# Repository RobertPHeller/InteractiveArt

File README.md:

# Interactive Art 

These are micro-processor based art projects where the viewer can interact in 
some way with the art.  These art items use Arduino and Arduino-like 
micro-processors to provide the "smarts" for the interactivity.

The projects include:

1. [Hello World](HelloWorld)
2. [Welcome To Gothem City](WelcomeToGothemCity)
3. [Paging Dr. Howard, Dr Fine, Dr. Howard](PagingDrHowardEtAl)
4. [Why Did The Chicken Cross The Street](WhyDidTheChicken)
5. [The Android's Dream](AndroidsDream)
6. [Only Her Hairdresser Knows For Sure](OnlyHerHairdresser)
7. [Sprocket Factory](SprocketFactory)
8. [Steel Wheels](SteelWheels)
9. [Stray Cats](StrayCats)

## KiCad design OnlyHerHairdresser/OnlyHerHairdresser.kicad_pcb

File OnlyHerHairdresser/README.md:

# Only Her Hairdresser Knows For Sure

This piece features a young lady who needs a little help deciding on a hair 
color.  The observer has a selection of hair colors to choose from.  By 
placing a selected "hair color box" (a painted wooden block) in the young 
lady's hand that color is applied to the fiber optic hair via RGB LEDs. The 
observer might want to try several selections.

## Processing Element

This piece uses an Adafruit Feather M0 Express.

## Components of Note

* Adafruit TCS34725  Breakout (Color Sensor).
* A MPQ3904 quad NPN driver transistor.
* Four 10mm RGB LEDs.
* Side glow fiber optics (used for the ``hair'').

## Additional Reading

* [_Fiber Optic Pixie Skirt_](https://learn.adafruit.com/fiber-optic-pixie-princess-skirt)
* [_Adafruit Color Sensors_](https://learn.adafruit.com/adafruit-color-sensors)

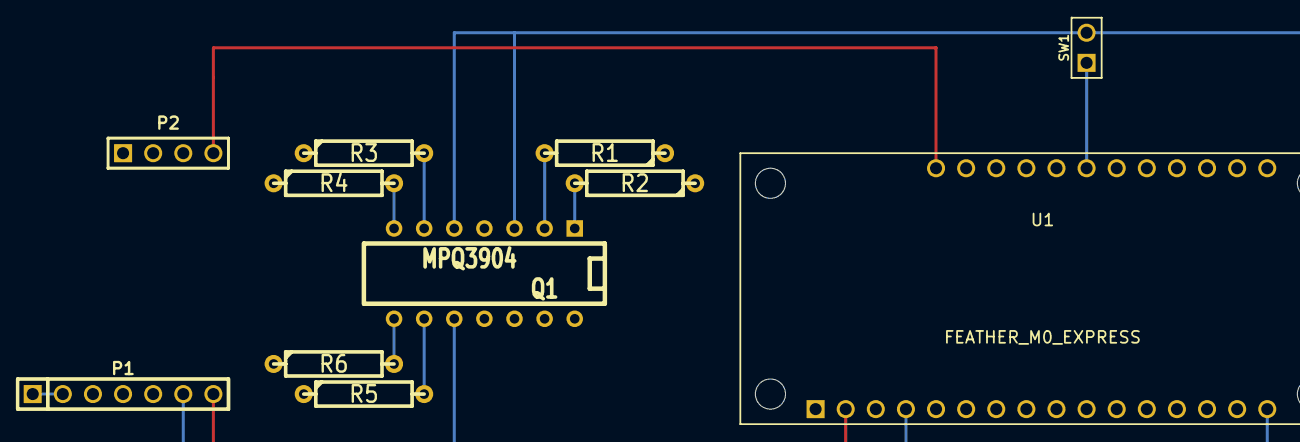
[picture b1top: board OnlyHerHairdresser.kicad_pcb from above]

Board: 6 copper layers, 11 parts (0 on the bottom side), 19 nets.

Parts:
P1: TCS34725 Breakout; PIN_ARRAY-7X1
P2: RGB LEDS; PIN_ARRAY_4x1
Q1: MPQ3904; DIP-14__300
R1, R3, R5: 1K Ohms; R4
R2, R4, R6: 45 Ohms; R4
SW1: SW_PUSH; PIN_ARRAY_2X1
U1: FEATHER_M0_EXPRESS; AdafruitFeather

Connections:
/B: P2.3, R6.1
/Comm: P2.4, U1.28
/G: P2.2, R4.1
/GND: P1.6, Q1.3, Q1.5, Q1.10, SW1.2, U1.4, U1.16
/INT: P1.1, P1.2
/R: P2.1, R2.1
/SCL: P1.4, U1.18
/SDA: P1.3, U1.17
/VIN: P1.7, U1.2
unnamed: Q1.1, R2.2
unnamed: Q1.7, R4.2
unnamed: Q1.8, R6.2
unnamed: SW1.1, U1.23
unnamed: Q1.2, R1.2
unnamed: Q1.9, R5.2
unnamed: R5.1, U1.19
unnamed: Q1.6, R3.2
unnamed: R3.1, U1.20
unnamed: R1.1, U1.22

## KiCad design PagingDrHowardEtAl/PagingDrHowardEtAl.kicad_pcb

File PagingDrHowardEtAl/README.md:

# Paging Dr. Howard, Dr. Fine, Dr. Howard

Oh dear, you are hospitalized with a bad case of humorititous. Fortunately,
the three top specialists of this condition are in residence and have agreed
to provide you with their world famous treatment. Dr. Moe Howard, Dr. Larry
Fine, and Dr. Curly Howard first need to check to see if you have a pulse
before you are wheeled into the operating theater, where they will operate on
your funny bone. Place your finger in the sensor hole and press down to check
your pulse.

## Processing Element

This piece uses a Arduino Uno processor.

## Components of Note

* World Famous Electronics Pulse Sensor
* Adafruit Bargraph Backpack
* Adafruit 7 segment backpack

## Additional Reading

* [_Super Awesome Sylvia Builds a Pulse Sensor Pendant_](https://makezine.com/2013/05/28/super-awesome-sylvia-builds-a-pulse-sensor-pendant/)
* [_Adafruit LED Backpacks_](https://learn.adafruit.com/adafruit-led-backpack/)

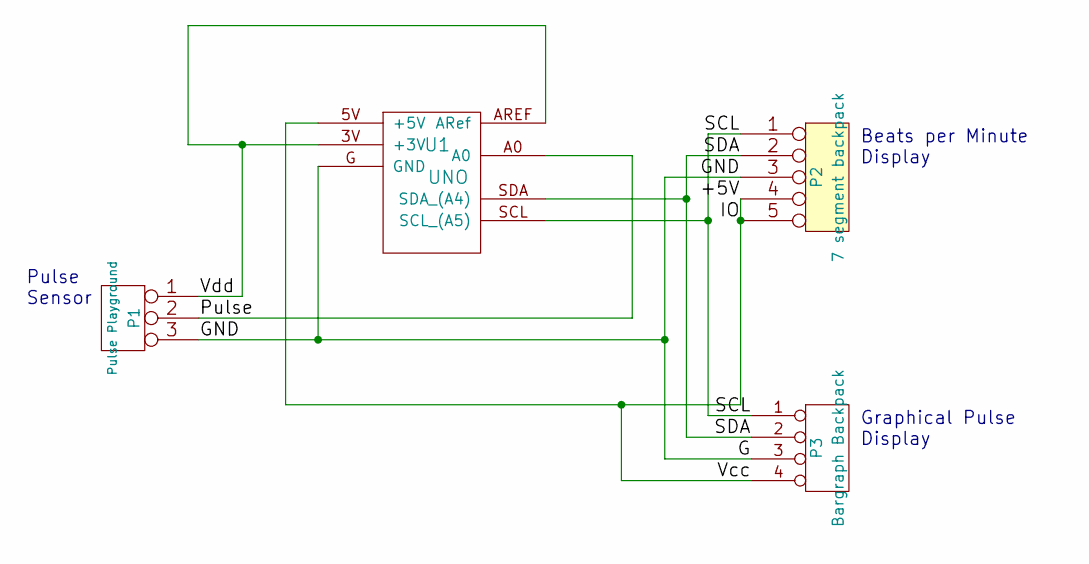
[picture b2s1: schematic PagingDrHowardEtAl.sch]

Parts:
P1: Pulse Playground
P2: 7 segment backpack
P3: Bargraph Backpack
U1: UNO

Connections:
/+5V: P2.4, P2.5, P3.4, U1.5V (+5V)
/G: P1.3, P2.3, P3.3, U1.G (GND)
/Pulse: P1.2 (PM), U1.A0
/SCL: P2.1, P3.1, U1.SCL (SCL_(A5))
/SDA: P2.2, P3.2, U1.SDA (SDA_(A4))
/Vdd: P1.1, U1.3V (+3V), U1.AREF (ARef)

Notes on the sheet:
Pulse Sensor
Beats per Minute Display
Graphical Pulse Display

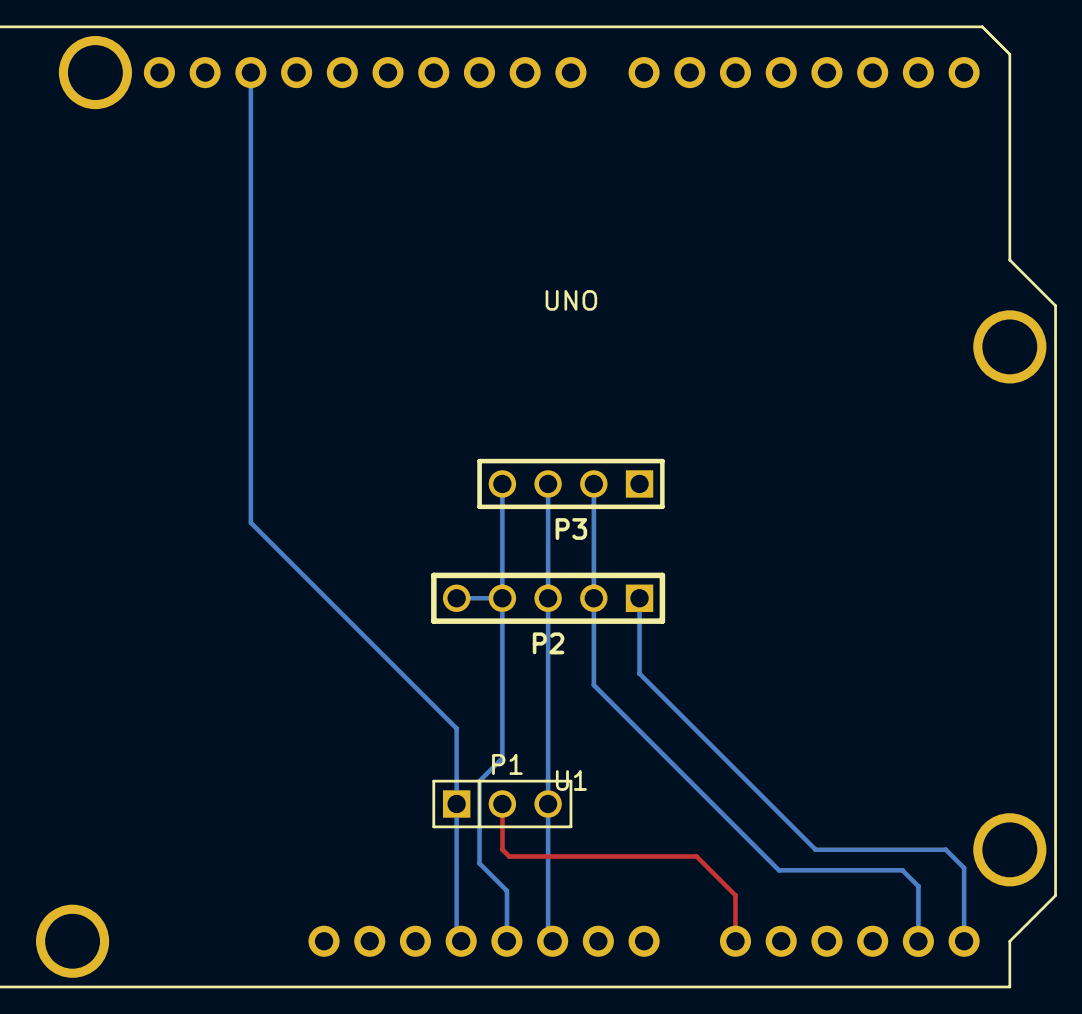
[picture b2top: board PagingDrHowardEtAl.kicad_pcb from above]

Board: 8 copper layers, 4 parts (0 on the bottom side), 6 nets.

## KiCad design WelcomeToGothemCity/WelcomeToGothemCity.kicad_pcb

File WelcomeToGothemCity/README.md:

# Welcome To Gothem City

Welcome to Gothem City, home of Batman and Robin. Oh no, the Bat Signal has
lit up the night as we get closer to the city. Does that mean there is a super
villain in town? See if you can find Batman and Robin or the super villain
(there may even be several). 

## Processing Element

This piece uses an Adafruit Metro Mini.

## Components of Note

* Adafruit Powerboost 1000c to provide extra power and to charge the battery.
* An SR04 ultrasonic range finder sensor.
* A TIP120 power transistor.
* A large number of yellow SMD LEDs to light up the Bat Signal.

## Additional Reading

* [_Distance Measurement with Ultrasound_](https://learn.adafruit.com/distance-measurement-ultrasound-hcsr04)

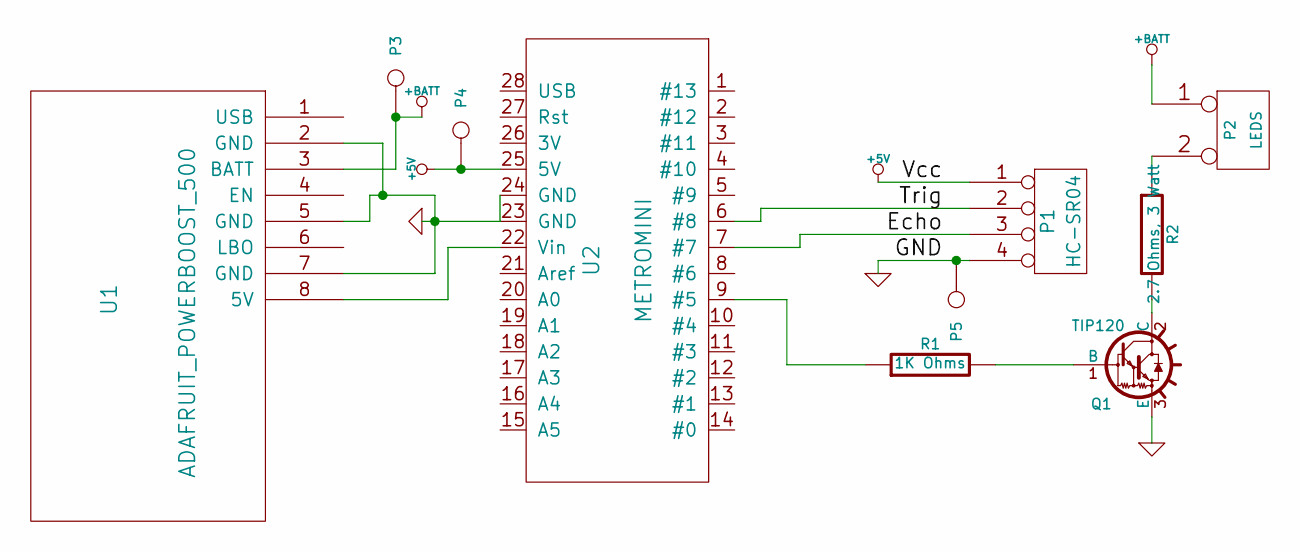
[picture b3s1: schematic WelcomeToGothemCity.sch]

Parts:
P1: HC-SR04
P2: LEDS
P3, P4, P5: CONN_1
Q1: TIP120; TO220
R1: 1K Ohms
R2: 2.7 Ohms, 3 Watt; Mouser Part Number 594-5093NW2R700J
U1: ADAFRUIT_POWERBOOST_500
U2: METROMINI

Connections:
+5V: P1.1, P4.1, U2.25 (5V)
+BATT: P2.1, P3.1, U1.3 (BATT)
/Echo: P1.3, U2.7 (#7)
/Trig: P1.2, U2.6 (#8)
GND: P1.4, P5.1, Q1.3 (E), U1.2 (GND), U1.5 (GND), U1.7 (GND), U2.23 (GND), U2.24 (GND)
unnamed: U1.8 (5V), U2.22 (Vin)
unnamed: P2.2 (PM), R2.1
unnamed: Q1.2 (C), R2.2
unnamed: Q1.1 (B), R1.2
unnamed: R1.1, U2.9 (#5)

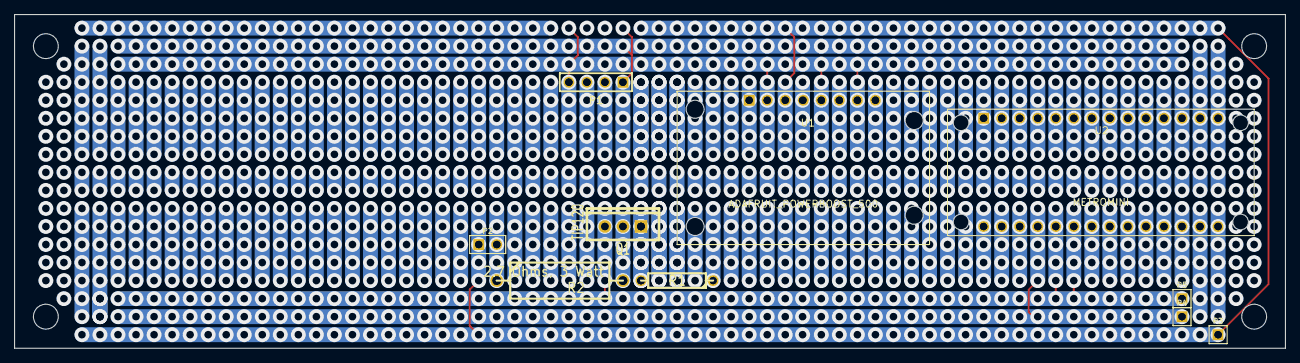
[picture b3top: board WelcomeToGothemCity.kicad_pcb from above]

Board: 8 copper layers, 179.0 x 47.0 mm, 10 parts (0 on the bottom side), 10 nets.

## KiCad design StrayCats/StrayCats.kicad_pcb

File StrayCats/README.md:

# Stray Cats

    Black and orange stray cat sittin' on a fence
    Ain't got enough dough to pay the rent
    I'm flat broke, but I don't care
    I strut right by with my tail in the air
    -- Brian Setzer

This piece features a small TV set that only gets channels featuring cats. Go 
ahead, use the remote to select a different channel.  Sorry, every channel 
features cats.

## Processing Element

This piece uses an Adafruit Feather M0 Express.

## Components of Note

* An Adafruit 1.8" TFT Display Breakout, that features a microSD card 
slot.
* An IR Detector and a mini remote control.

## Additional Reading

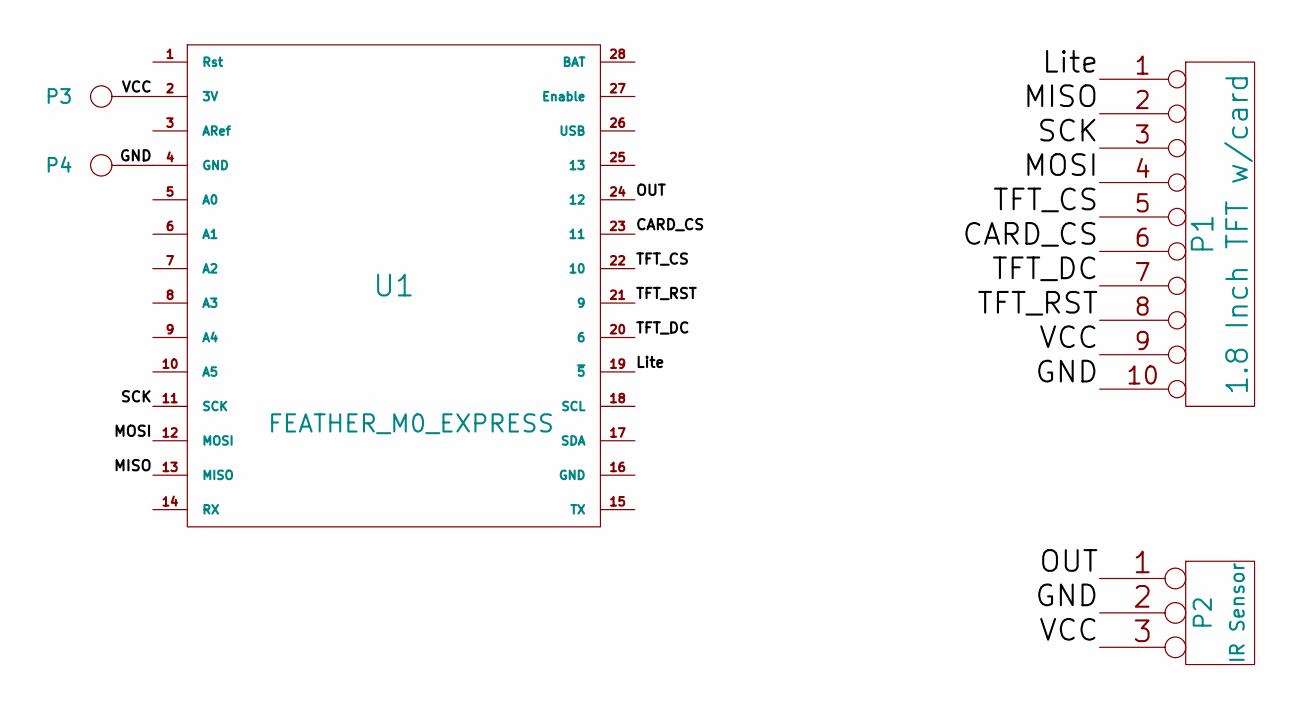
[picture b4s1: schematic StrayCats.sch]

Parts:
P1: 1.8 Inch TFT w/card
P2: IR Sensor
P3, P4: CONN_1
U1: FEATHER_M0_EXPRESS

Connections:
/CARD_CS: P1.6, U1.23 (11~)
/GND: P1.10, P2.2 (PM), P4.1, U1.4 (GND)
/Lite: P1.1, U1.19 (~5)
/MISO: P1.2, U1.13 (MISO)
/MOSI: P1.4, U1.12 (MOSI)
/OUT: P2.1, U1.24 (12)
/SCK: P1.3, U1.11 (SCK)
/TFT_CS: P1.5, U1.22 (10~)
/TFT_DC: P1.7, U1.20 (6)
/TFT_RST: P1.8, U1.21 (9~)
/VCC: P1.9, P2.3, P3.1, U1.2 (3V)

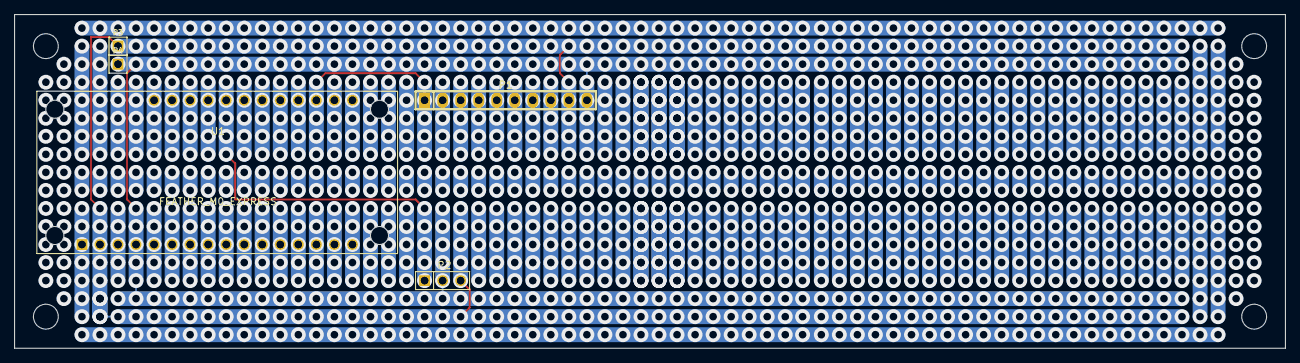
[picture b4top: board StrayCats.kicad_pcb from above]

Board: 8 copper layers, 179.0 x 47.0 mm, 5 parts (0 on the bottom side), 11 nets.

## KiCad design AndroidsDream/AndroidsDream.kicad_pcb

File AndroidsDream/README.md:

# The Androids Dream

This piece was inspired by the question posed in the title of a Philip K. Dick
novel, _Do Androids Dream Of Electric Sheep?_. This piece features an
electric sheep, so it is possibly what every android is dreaming of. This not
merely a stuffed sheep toy, it actually moves like a real sheep, but is
powered by electricity and not by grass (yes, the grass it is lying on is fake
too). Go ahead and pet it. It will raise its head and wag its tail. Don't you
wish you were an android so that this would be the answer to your dreams?

## Processing Element

This piece uses a 3V Adafruit Itsy Bitsy 32u4.

## Components of Note

* A pair of micro servos (to move the head and tail).
* Three Light Dependent Resistors (light sensors) to sense when it is dark
(sleep mode) or when being petted.
* Two micro servos to move the head and tail.

## Additional Reading

* [_Adafruit Trinket-Modded Stuffed Animal_](https://learn.adafruit.com/adafruit-trinket-modded-stuffed-animal)

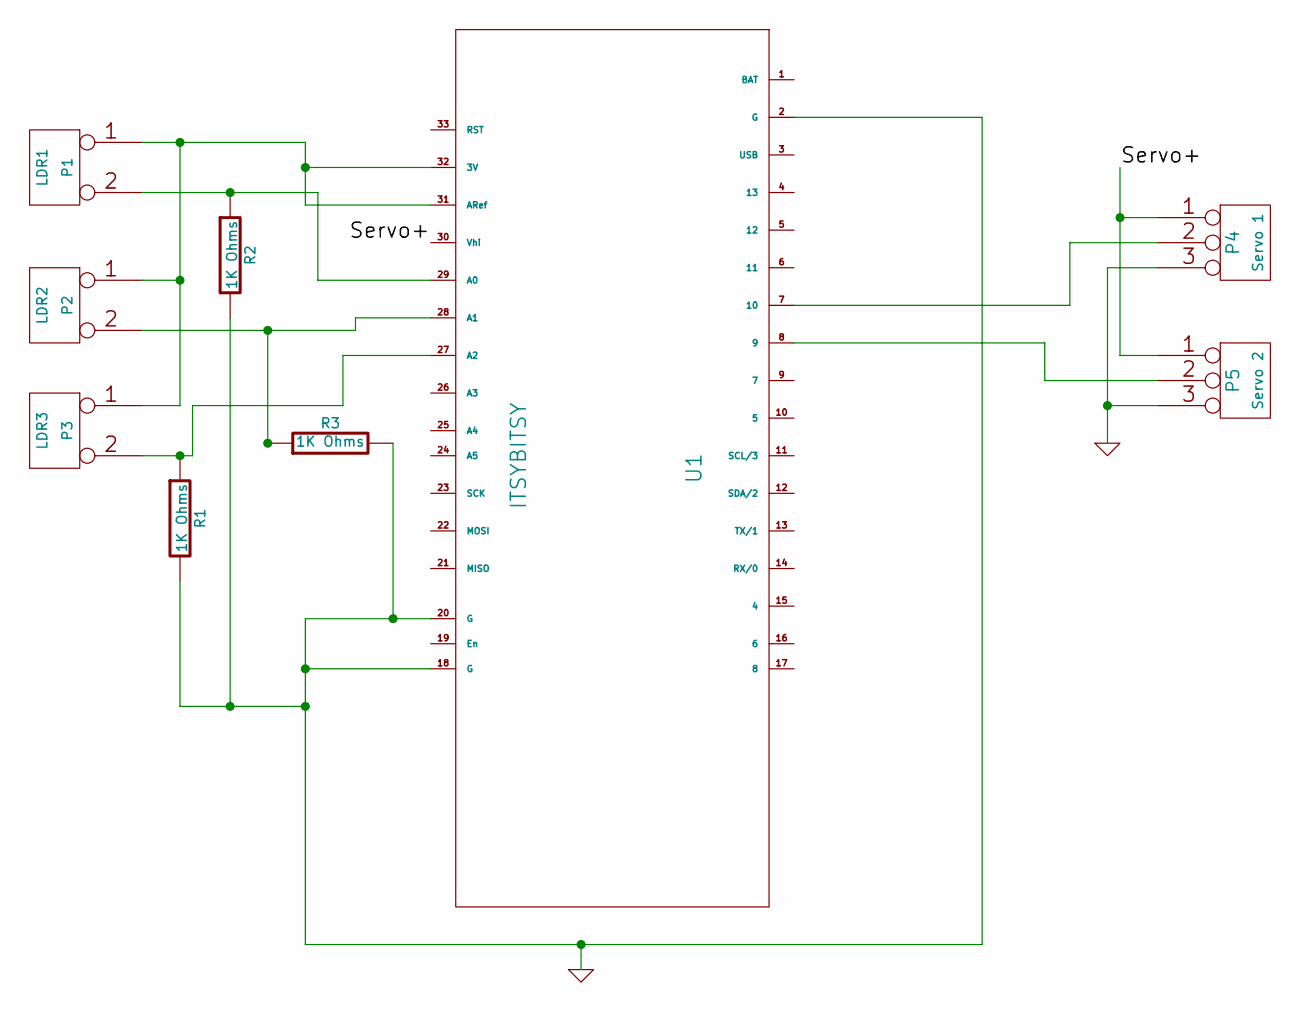
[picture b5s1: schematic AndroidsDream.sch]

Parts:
P1: LDR1
P2: LDR2
P3: LDR3
P4: Servo 1
P5: Servo 2
R1, R2, R3: 1K Ohms
U1: ITSYBITSY

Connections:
/Servo+: P4.1, P5.1, U1.30 (Vhi)
GND: P4.3, P5.3, R1.2, R2.2, R3.2, U1.2 (G), U1.18 (G), U1.20 (G)
unnamed: P4.2 (PM), U1.7 (10)
unnamed: P5.2 (PM), U1.8 (9)
unnamed: P1.1, P2.1, P3.1, U1.31 (ARef), U1.32 (3V)
unnamed: P2.2 (PM), R3.1, U1.28 (A1)
unnamed: P1.2 (PM), R2.1, U1.29 (A0)
unnamed: P3.2 (PM), R1.1, U1.27 (A2)

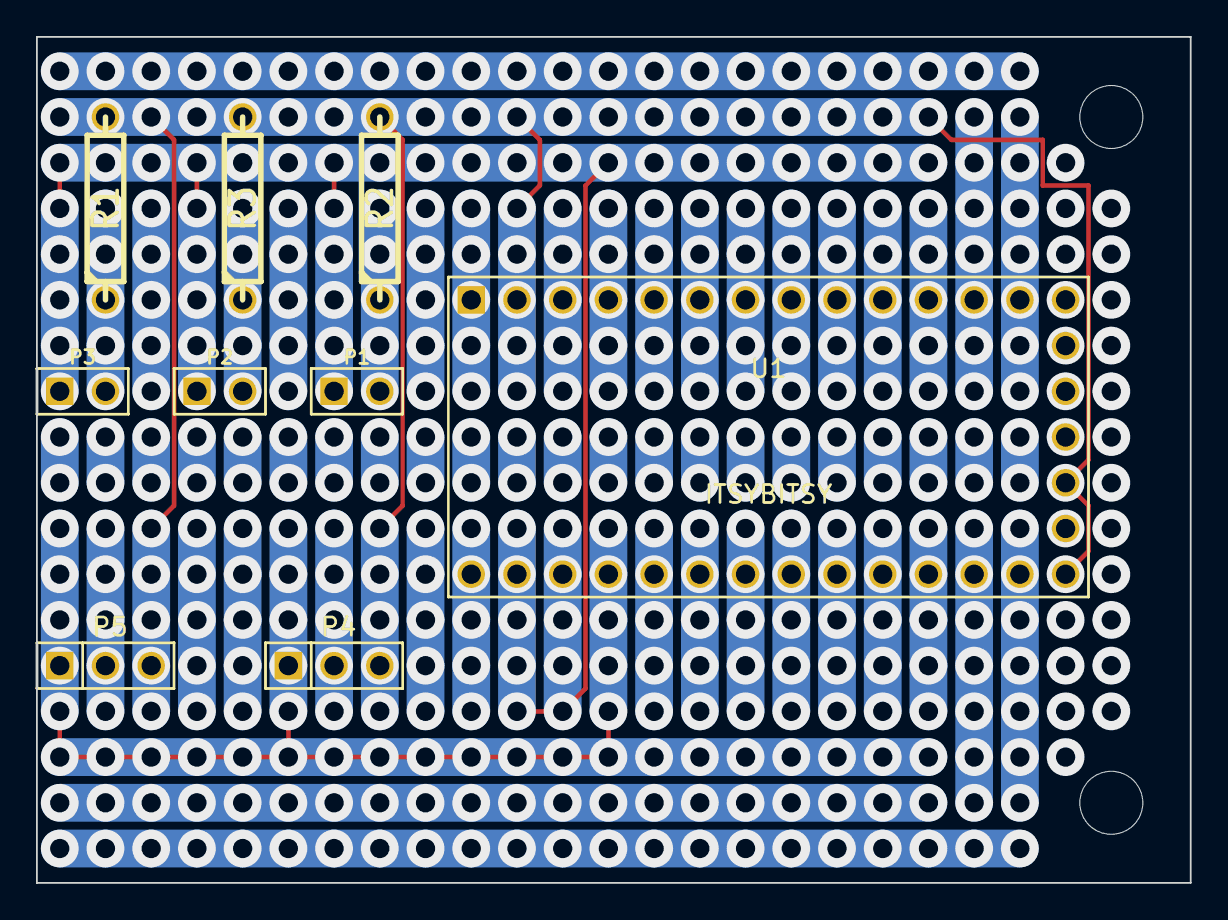
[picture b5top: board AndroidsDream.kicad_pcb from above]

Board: 8 copper layers, 64.1 x 47.0 mm, 9 parts (0 on the bottom side), 8 nets.

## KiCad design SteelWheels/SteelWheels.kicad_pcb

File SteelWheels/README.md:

# Steel Wheels

Great news, you have been hired to be the engineer of a steam locomotive. 
You get to use the throttle to make it go fast or slow.  Go ahead crank the 
throttle to its maximum.  Full stream ahead!

## Processing Element

This piece uses an Adafruit Metro Mini.

## Components of Note

* Two small twelve pixel Neopixel rings.
* Two large twenty four pixel Neopixel rings.
* One quarter segment giant Neopixel ring.

## Additional Reading}

* [_The Magic of NeoPixels_](https://learn.adafruit.com/adafruit-neopixel-uberguide)

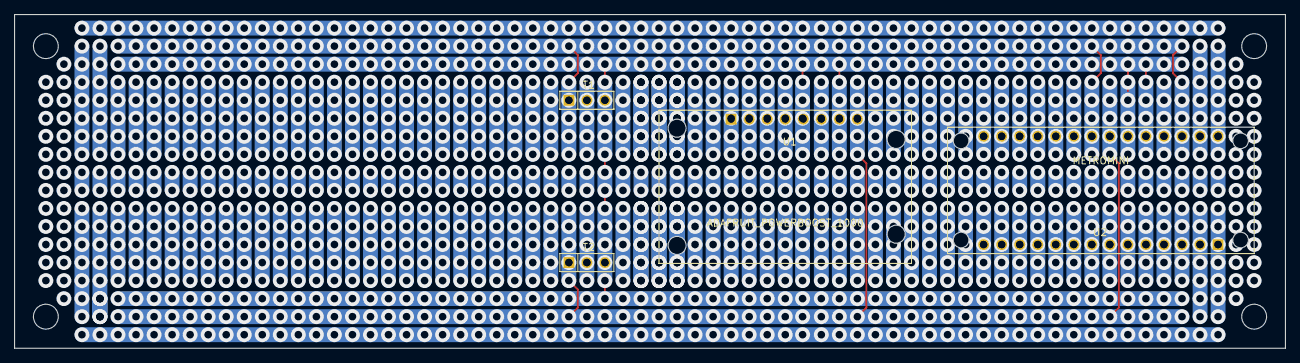
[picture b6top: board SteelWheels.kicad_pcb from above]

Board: 8 copper layers, 179.0 x 47.0 mm, 4 parts (0 on the bottom side), 5 nets.

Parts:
T1: Throttle; PIN_ARRAY_3X1
T2: Neopixels; PIN_ARRAY_3X1
U1: ADAFRUIT_POWERBOOST_1000; PBost500Breakout
U2: METROMINI; MetroMini

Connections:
+3.3V: T1.1, U2.21, U2.26
+5V: T2.1, U1.8, U2.22
/ThrottleIn: T1.2, U2.20
GND: T1.3, T2.3, U1.5, U1.7, U2.23, U2.24
unnamed: T2.2, U2.8

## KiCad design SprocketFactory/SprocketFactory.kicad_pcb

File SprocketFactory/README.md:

# Sprocket Factory

Congratulations, you have been promoted to VP of Production at the sprocket
factory. You job consists of pressing the Start button promptly at 9:00am each
morning and then pressing the Stop button promptly at 5:00pm each evening. Go
ahead press the start button now to get the fully automated factory going.
Don't forget to press the Stop button before you leave for the day.

## Processing Element

This piece uses an Adafruit Feather M0 Express.

## Components of Note

* Adafruit 8 channel PWM or Servo Feather Wing.
* Adafruit Powerboost 1000c.
* 8 Micro Servos

## Additional Reading

* [_Adafruit 8-Channel PWM or Servo FeatherWing_](https://learn.adafruit.com/adafruit-8-channel-pwm-or-servo-featherwing)

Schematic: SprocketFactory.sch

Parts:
SW1: Start
SW2: Stop
U1: FEATHER_M0_EXPRESS
U2: 8-CHANNELSERVO​FEATHERWING
U3: ADAFRUIT_POWERBOOST_500

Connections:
/3V: U1.2 (3V), U2.2
/5: SW2.1, U1.19 (~5), U2.19
/6: SW1.1, U1.20 (6), U2.20
/9: U1.21 (9~), U2.21
/10: U1.22 (10~), U2.22
/11: U1.23 (11~), U2.23
/12: U1.24 (12), U2.24
/13: U1.25 (13), U2.25
/A0: U1.5 (A0), U2.5
/A1: U1.6 (A1), U2.6
/A2: U1.7 (A2), U2.7
/A3: U1.8 (A3), U2.8
/A4: U1.9 (A4), U2.9
/A5: U1.10 (A5), U2.10
/ARef: U1.3 (ARef), U2.3
/BAT: U1.28 (BAT), U2.28, U3.3 (BATT)
/Enable: U1.27 (Enable), U2.27
/GND: SW1.2, SW2.2, U1.4 (GND), U1.16 (GND), U2.4, U2.16, U2.SP-, U3.2 (GND), U3.5 (GND), U3.7 (GND)
/MISO: U1.13 (MISO), U2.13
/MOSI: U1.12 (MOSI), U2.12
/RX: U1.14 (RX), U2.14
/Rst: U1.1 (Rst), U2.1
/SCK: U1.11 (SCK), U2.11
/SCL: U1.18 (SCL), U2.18
/SDA: U1.17 (SDA), U2.17
/TX: U1.15 (TX), U2.15
/USB: U1.26 (USB), U2.26
unnamed: U2.SP+, U3.8 (5V)

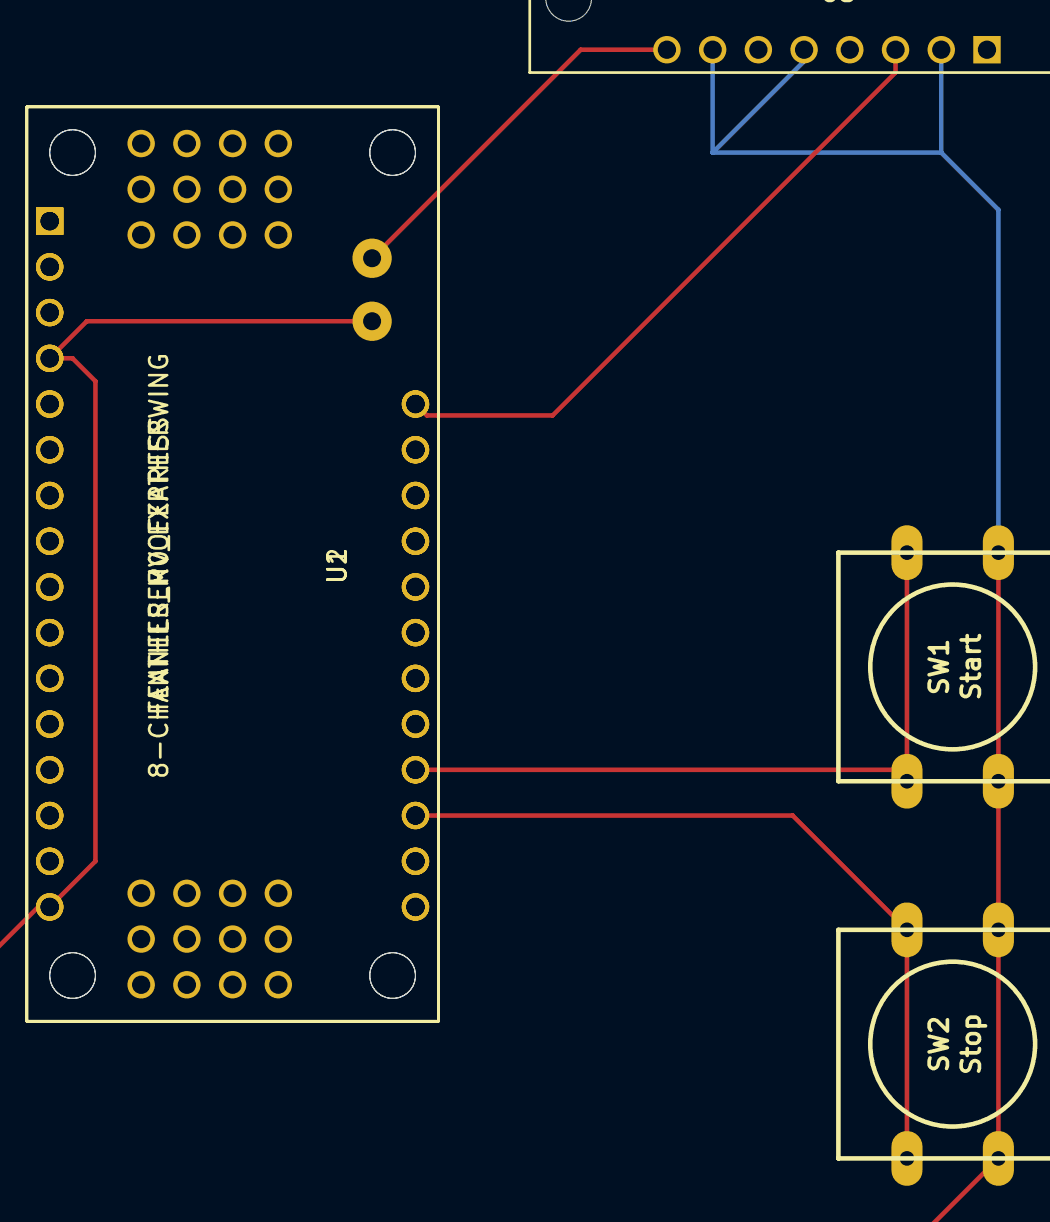
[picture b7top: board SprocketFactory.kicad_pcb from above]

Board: 2 copper layers, 5 parts (0 on the bottom side), 28 nets.

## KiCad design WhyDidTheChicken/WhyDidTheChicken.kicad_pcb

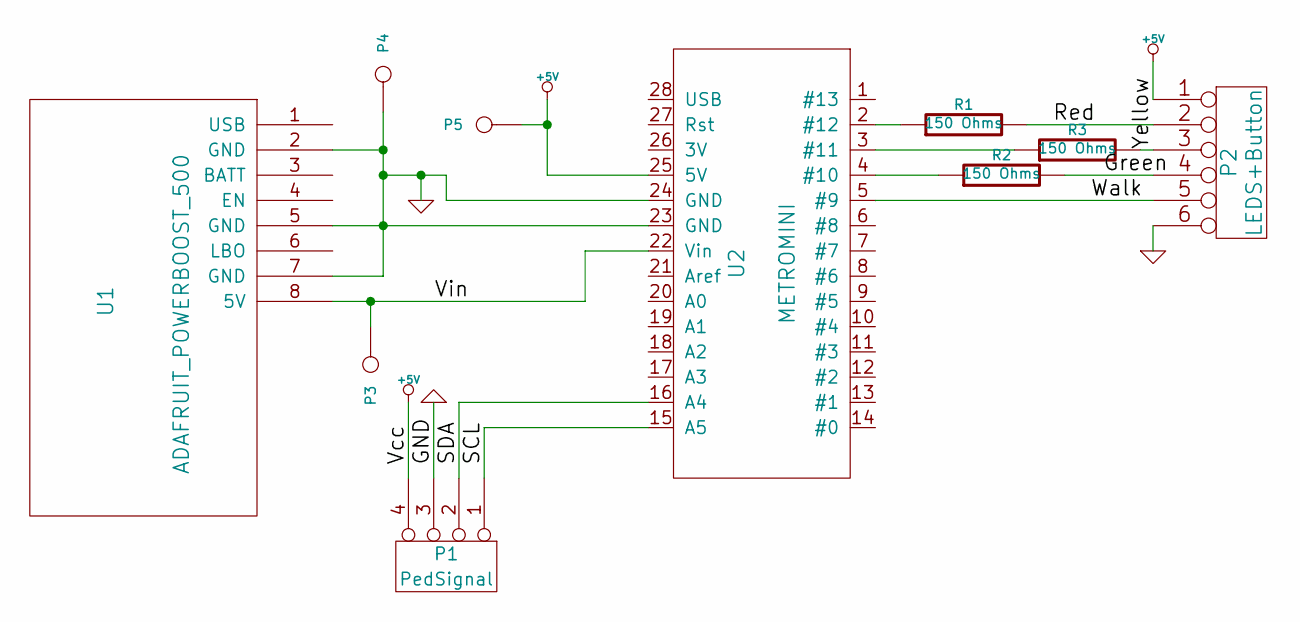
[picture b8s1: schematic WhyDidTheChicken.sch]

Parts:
P1: PedSignal
P2: LEDS+Button
P3, P4, P5: CONN_1
R1, R2, R3: 150 Ohms
U1: ADAFRUIT_POWERBOOST_500
U2: METROMINI

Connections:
+5V: P1.4, P2.1, P5.1, U2.25 (5V)
/Green: P2.4, R2.2
/Red: P2.2, R1.2
/SCL: P1.1, U2.15 (A5)
/SDA: P1.2, U2.16 (A4)
/Vin: P3.1, U1.8 (5V), U2.22 (Vin)
/Walk: P2.5, U2.5 (#9)
/Yellow: P2.3, R3.2
GND: P1.3, P2.6, P4.1, U1.2 (GND), U1.5 (GND), U1.7 (GND), U2.23 (GND), U2.24 (GND)
unnamed: R2.1, U2.4 (#10)
unnamed: R3.1, U2.3 (#11)
unnamed: R1.1, U2.2 (#12)

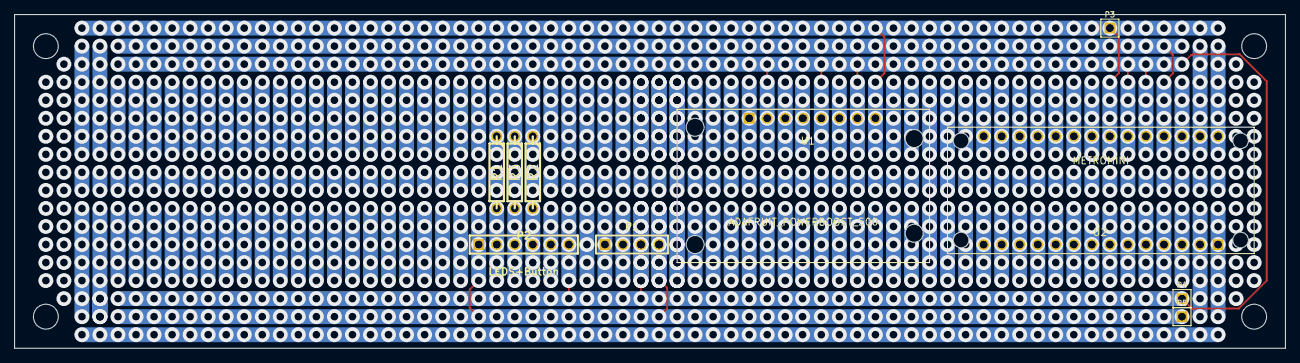
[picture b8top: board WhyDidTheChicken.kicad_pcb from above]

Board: 8 copper layers, 179.0 x 47.0 mm, 10 parts (0 on the bottom side), 12 nets.

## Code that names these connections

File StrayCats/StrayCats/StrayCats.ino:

// -!- C++ -!- //////////////////////////////////////////////////////////////
//
//  System        : 
//  Module        : 
//  Object Name   : $RCSfile$
//  Revision      : $Revision$
//  Date          : $Date$
//  Author        : $Author$
//  Created By    : $USER_NAME$
//  Created       : $ASCII_TIME$
//  Last Modified : <181229.1757>
//
//  Description	
//
//  Notes
//
//  History
//	
/////////////////////////////////////////////////////////////////////////////
//
//    Copyright (C) $YEAR$  Robert Heller D/B/A Deepwoods Software
//			51 Locke Hill Road
//			Wendell, MA 01379-9728
//
//    This program is free software; you can redistribute it and/or modify
//    it under the terms of the GNU General Public License as published by
//    the Free Software Foundation; either version 2 of the License, or
//    (at your option) any later version.
//
//    This program is distributed in the hope that it will be useful,
//    but WITHOUT ANY WARRANTY; without even the implied warranty of
//    MERCHANTABILITY or FITNESS FOR A PARTICULAR PURPOSE.  See the
//    GNU General Public License for more details.
//
//    You should have received a copy of the GNU General Public License
//    along with this program; if not, write to the Free Software
//    Foundation, Inc., 675 Mass Ave, Cambridge, MA 02139, USA.
//
// 
//
//////////////////////////////////////////////////////////////////////////////

static const char rcsid[] = "@(#) : $Id$";

#include <Adafruit_ST7735.h>
#include <Adafruit_GFX.h>
#include <SD.h>
#include "IRRemote.h"
#include <string.h>

#define CARD_CS 11
#define TFT_CS  10
#define TFT_RST  9
#define TFT_DC   6
#define Lite     5

Adafruit_ST7735 display = Adafruit_ST7735(TFT_CS,TFT_DC,TFT_RST);
RemoteControl remote = RemoteControl();

int brightness;

// This function opens a Windows Bitmap (BMP) file and
// displays it at the given coordinates.  It's sped up
// by reading many pixels worth of data at a time
// (rather than pixel by pixel).  Increasing the buffer
// size takes more of the Arduino's precious RAM but
// makes loading a little faster.  20 pixels seems a
// good balance.

#define BUFFPIXEL 20

void bmpDraw(char *filename, uint8_t x, uint8_t y) {

  File     bmpFile;
  int      bmpWidth, bmpHeight;   // W+H in pixels
  uint8_t  bmpDepth;              // Bit depth (currently must be 24)
  uint32_t bmpImageoffset;        // Start of image data in file
  uint32_t rowSize;               // Not always = bmpWidth; may have padding
  uint8_t  sdbuffer[3*BUFFPIXEL]; // pixel buffer (R+G+B per pixel)
  uint8_t  buffidx = sizeof(sdbuffer); // Current position in sdbuffer
  boolean  goodBmp = false;       // Set to true on valid header parse
  boolean  flip    = true;        // BMP is stored bottom-to-top
  int      w, h, row, col;
  uint8_t  r, g, b;
  uint32_t pos = 0, startTime = millis();

  if((x >= display.width()) || (y >= display.height())) return;

  Serial.println();
  Serial.print("Loading image '");
  Serial.print(filename);
  Serial.println('\'');

  // Open requested file on SD card
  if ((bmpFile = SD.open(filename)) == NULL) {
    Serial.print("File not found");
    return;
  }

  // Parse BMP header
  if(read16(bmpFile) == 0x4D42) { // BMP signature
    Serial.print("File size: "); Serial.println(read32(bmpFile));
    (void)read32(bmpFile); // Read & ignore creator bytes
    bmpImageoffset = read32(bmpFile); // Start of image data
    Serial.print("Image Offset: "); Serial.println(bmpImageoffset, DEC);
    // Read DIB header
    Serial.print("Header size: "); Serial.println(read32(bmpFile));
    bmpWidth  = read32(bmpFile);
    bmpHeight = read32(bmpFile);
    if(read16(bmpFile) == 1) { // # planes -- must be '1'
      bmpDepth = read16(bmpFile); // bits per pixel
      Serial.print("Bit Depth: "); Serial.println(bmpDepth);
      if((bmpDepth == 24) && (read32(bmpFile) == 0)) { // 0 = uncompressed

        goodBmp = true; // Supported BMP format -- proceed!
        Serial.print("Image size: ");
        Serial.print(bmpWidth);
        Serial.print('x');
        Serial.println(bmpHeight);

        // BMP rows are padded (if needed) to 4-byte boundary
        rowSize = (bmpWidth * 3 + 3) & ~3;

        // If bmpHeight is negative, image is in top-down order.
        // This is not canon but has been observed in the wild.
        if(bmpHeight < 0) {
          bmpHeight = -bmpHeight;
          flip      = false;
        }

        // Crop area to be loaded
        w = bmpWidth;
        h = bmpHeight;
        if((x+w-1) >= display.width())  w = display.width()  - x;
        if((y+h-1) >= display.height()) h = display.height() - y;

        // Set TFT address window to clipped image bounds
        display.setAddrWindow(x, y, x+w-1, y+h-1);

        for (row=0; row<h; row++) { // For each scanline...

          // Seek to start of scan line.  It might seem labor-
          // intensive to be doing this on every line, but this
          // method covers a lot of gritty details like cropping
          // and scanline padding.  Also, the seek only takes
          // place if the file position actually needs to change
          // (avoids a lot of cluster math in SD library).
          if(flip) // Bitmap is stored bottom-to-top order (normal BMP)
            pos = bmpImageoffset + (bmpHeight - 1 - row) * rowSize;
          else     // Bitmap is stored top-to-bottom
            pos = bmpImageoffset + row * rowSize;
          if(bmpFile.position() != pos) { // Need seek?
            bmpFile.seek(pos);
            buffidx = sizeof(sdbuffer); // Force buffer reload
          }

          for (col=0; col<w; col++) { // For each pixel...
            // Time to read more pixel data?
            if (buffidx >= sizeof(sdbuffer)) { // Indeed
              bmpFile.read(sdbuffer, sizeof(sdbuffer));
              buffidx = 0; // Set index to beginning
            }

            // Convert pixel from BMP to TFT format, push to display
            b = sdbuffer[buffidx++];
            g = sdbuffer[buffidx++];
            r = sdbuffer[buffidx++];
            display.pushColor(display.Color565(r,g,b));
          } // end pixel
        } // end scanline
        Serial.print("Loaded in ");
        Serial.print(millis() - startTime);
        Serial.println(" ms");
      } // end goodBmp
    }
  }

  bmpFile.close();
  if(!goodBmp) Serial.println("BMP format not recognized.");
}

// These read 16- and 32-bit types from the SD card file.
// BMP data is stored little-endian, Arduino is little-endian too.
// May need to reverse subscript order if porting elsewhere.

uint16_t read16(File f) {
  uint16_t result;
  ((uint8_t *)&result)[0] = f.read(); // LSB
  ((uint8_t *)&result)[1] = f.read(); // MSB
  return result;
}

uint32_t read32(File f) {
  uint32_t result;
  ((uint8_t *)&result)[0] = f.read(); // LSB
  ((uint8_t *)&result)[1] = f.read();
  ((uint8_t *)&result)[2] = f.read();
  ((uint8_t *)&result)[3] = f.read(); // MSB
  return result;
}

#define LEARN

void setup() {
    SD.begin(CARD_CS);
#ifdef LEARN
    Serial.begin(9600);
    while (!Serial) {
        ; // wait for serial port to connect. Needed for native USB port only
    }
    Serial.println("Learn Mode...");
    remote.storePulses("VolM",'v');
    remote.storePulses("PlayPause",'p');
    remote.storePulses("VolP",'V');
    remote.storePulses("Setup",'s');
    remote.storePulses("Prev",'<');
    remote.storePulses("Stop",'S');
    remote.storePulses("ChM",'c');
    remote.storePulses("Enter",'e');
    remote.storePulses("ChP",'C');
    remote.storePulses("Zero",'0');
    remote.storePulses("Next",'>');
    remote.storePulses("Back",'b');
    remote.storePulses("One",'1');
    remote.storePulses("Two",'2');
    remote.storePulses("Three",'3');
    remote.storePulses("Four",'4');
    remote.storePulses("Five",'5');
    remote.storePulses("Six",'6');
    remote.storePulses("Seven",'7');
    remote.storePulses("Eight",'8');
    remote.storePulses("Nine",'9');
    Serial.println("Done");
#else
    brightness = 0;
    pinMode(Lite,OUTPUT);
    // Use this initializer if you're using a 1.8" TFT
    display.initR(INITR_BLACKTAB);
    display.setRotation(1); // Check...
#endif
}

void loop() {
#ifdef LEARN
    delay(10000);
#else
    int key = remote.listen();
    if (key < 0) {
        if (brightness > 0) {
            brightness--;
            analogWrite(Lite,brightness);
        }
    } else {
        char imagefile[10];
        strcpy(imagefile,"image_");
        imagefile[6] = key;
        strcpy(&imagefile[7],".bmp");
        bmpDraw(imagefile,0,0);
        brightness = 255;
        analogWrite(Lite,brightness);
    }
    delay(500);
#endif
}

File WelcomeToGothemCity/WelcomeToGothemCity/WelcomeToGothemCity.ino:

// -!- C++ -!- //////////////////////////////////////////////////////////////
//
//  System        : 
//  Module        : 
//  Object Name   : $RCSfile$
//  Revision      : $Revision$
//  Date          : $Date$
//  Author        : $Author$
//  Created By    : $USER_NAME$
//  Created       : $ASCII_TIME$
//  Last Modified : <190729.0003>
//
//  Description	
//
//  Notes
//
//  History
//	
/////////////////////////////////////////////////////////////////////////////
//
//    Copyright (C) $YEAR$  Robert Heller D/B/A Deepwoods Software
//			51 Locke Hill Road
//			Wendell, MA 01379-9728
//
//    This program is free software; you can redistribute it and/or modify
//    it under the terms of the GNU General Public License as published by
//    the Free Software Foundation; either version 2 of the License, or
//    (at your option) any later version.
//
//    This program is distributed in the hope that it will be useful,
//    but WITHOUT ANY WARRANTY; without even the implied warranty of
//    MERCHANTABILITY or FITNESS FOR A PARTICULAR PURPOSE.  See the
//    GNU General Public License for more details.
//
//    You should have received a copy of the GNU General Public License
//    along with this program; if not, write to the Free Software
//    Foundation, Inc., 675 Mass Ave, Cambridge, MA 02139, USA.
//
// 
//
//////////////////////////////////////////////////////////////////////////////

static const char rcsid[] = "@(#) : $Id$";

// SR04 Data pins
const int TRIG_PIN = 8;
const int ECHO_PIN = 7;
// LEDs pin
const int LEDS     = 5;


// Anything over 400 cm (23200 us pulse) is "out of range"
const unsigned int MAX_DIST = 23200;

// Distance thresholds
const float CLOSE_INCHES = 2.5;
const float NEAR_INCHES  = 5.0;
const float FAR_INCHES   = 10.0;
const float VERY_FAR_INCHES = 15.0;
const float DISTANT_INCHES  = 30.0;


//**************************************************************
//* Setup: set pinmodes, turn off LEDs                         *
//**************************************************************
void setup() {
    Serial.begin(9600);
    // The Trigger pin will tell the sensor to range find
    pinMode(TRIG_PIN, OUTPUT);
    pinMode(ECHO_PIN, INPUT);
    digitalWrite(TRIG_PIN, LOW);
    
    pinMode(LEDS, OUTPUT);
    pinMode(LED_BUILTIN, OUTPUT);
    //digitalWrite(LEDS,0);
    analogWrite(LEDS,0);
}

//**************************************************************
//* Main Loop:  Trigger the sensor and retreive a result pulse *
//*             Compute the pulse width to measure the distance*
//*             Compare the measured distance to the thresholds*
//*             and light the LEDs to the selected brightness. *
//**************************************************************
void loop() {
    unsigned long t1;
    unsigned long t2;
    unsigned long pulse_width;
    float cm;
    float inches;
    
    // Hold the trigger pin high for at least 10 us
    digitalWrite(TRIG_PIN, HIGH);
    delayMicroseconds(10);
    digitalWrite(TRIG_PIN, LOW);
    
    // Wait for pulse on echo pin
    while ( digitalRead(ECHO_PIN) == 0 );
    
    // Measure how long the echo pin was held high (pulse width)
    // Note: the micros() counter will overflow after ~70 min
    t1 = micros();
    while ( digitalRead(ECHO_PIN) == 1);
    t2 = micros();
    pulse_width = t2 - t1;
    
    //Serial.print("*** pulse_width = ");Serial.println(pulse_width);
    // Calculate distance in centimeters and inches. The constants
    // are found in the datasheet, and calculated from the assumed speed 
    //of sound in air at sea level (~340 m/s).
    inches = pulse_width / 148.0;
    
    //Serial.print("*** inch = ");Serial.println(inches);
    // Measure thresholds and light the LEDs to the brightness called for.
    if (inches < CLOSE_INCHES) {
        //digitalWrite(LEDS,1);
        digitalWrite(LED_BUILTIN,1);
        Serial.println("CLOSE_INCHES");
        analogWrite(LEDS,255); // Very close, full brightness
    } else if (inches < NEAR_INCHES) {
        //digitalWrite(LEDS,1);
        digitalWrite(LED_BUILTIN,1);
        Serial.println("NEAR_INCHES");
        analogWrite(LEDS,192); // Pretty near, medium bright
    } else if (inches < FAR_INCHES) {
        Serial.println("FAR_INCHES");
        analogWrite(LEDS,128); // Fairly far, low brightness
    } else if (inches < VERY_FAR_INCHES) {
        Serial.println("VERY_FAR_INCHES");
        analogWrite(LEDS,64); // Very far, dim
    } else if (inches < DISTANT_INCHES) {
        Serial.println("DISTANT_INCHES");
        analogWrite(LEDS,32); // Very, very far very dim
    } else {
        Serial.println("Beyond DISTANT_INCHES");
        //digitalWrite(LEDS,0);
        digitalWrite(LED_BUILTIN,0);
        analogWrite(LEDS,0);  // Too far, totally dark
    }
    delay(100); // Check again in a 1/10 of a second.
}

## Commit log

2018-06-27 Initialize Repository
2018-06-27 Title list
2018-06-29 Create modules for Adafuit parts
2018-06-29 Create some of the piece projects
2018-10-22 (Re-)Initialize project
2018-10-24 Add Arduno project sketches.
2018-10-24 Complete infrastructure reorganization.
2018-10-25 HelloWorld Bitmap library.
2018-10-25 Final tweaks to the Hello World circuit.
2018-10-25 Hello World firmware completed.
2018-10-25 Add Comment headers to sketches.
2018-10-26 Complete Welcome To Gothem City
2018-10-26 Minor tweaks to WelcomeToGothemCity
2018-10-28 Complete two more: WelcomeToGothemCity and WhyDidTheChicken
2018-11-01 Completed SprocketFactory
2018-11-01 Update WelcomeToGothemCity: actual value for R2
2018-11-03 OnlyHerHairdresser: circuit designed and board laid out
2018-11-03 Completed code for OnlyHerHairdresser
2018-11-03 Minor tweaks to OnlyHerHairdresser
2018-11-03 Final debugging of Hello_World code.
2018-11-04 Completed SteelWheels
2018-11-05 Completed AndoidsDream.
2018-11-05 Complete PagingDrHowardEtAl
2018-11-06 Create cityscape generator
2018-11-06 Include variable initialization in setup()
2018-11-07 Additional tweaks to GenerateGothemCity.tcl
2018-11-07 Create program to blow up THE-THREE-STOOGES
2018-11-07 Generialize Enlarge.tcl
2018-11-08 Rename Hello_World to HelloWorld
2018-11-08 Start work on writeups
2018-11-08 Continue work on writeups
2018-11-09 Add QR Codes for all of the URLs
2018-11-10 Completed first draft of writups
2018-11-10 Include makefile for writups
2018-11-10 Continue writeups
2018-11-10 Rename misspelled directory and file names (AndoidsDream => AndroidsDream)
2018-11-10 Complete draft of writeup, with additional reading sections.
2018-11-11 Tweaks to the writups
2018-11-11 Add contact info to writeup
2018-11-11 Add PDFs of the Schematics
2018-11-11 Add detailed comments to both the code and the schematics
2018-11-11 Add 30ms debounce delay
2018-12-01 Add personal website to writeup, minor typos fixed in the writeup.
2018-12-04 Tweaks to writeup
2018-12-05 Minor fixes to WelcomeToGothemCity PCB
2018-12-29 Add the StrayCats piece.
2018-12-29 Minor update to StrayCats.ino
2019-01-13 Update WelcomeToGothemCity PCB (correct orientation of SR04 connector).
2019-01-17 Update TheGamesAFoot code.
2019-01-17 Fix transistor module (correct pin ordering).
2019-08-03 Add villian images, etc.
2019-08-04 Final debugging of WelcomeToGothemCity.
2019-08-27 Improved Hello World.
2019-08-27 Update PagingDrHowardEtAl.
2019-08-27 Revert "Improved Hello World."
    This reverts commit 9cfeab49f8a40077d410afd7f5da9c114483a884.
2019-08-27 Revert "Revert "Improved Hello World.""
    This reverts commit 68956442f3c98f9f4d55407133d2008b60599163.
2019-08-27 Revert "Update PagingDrHowardEtAl."
    This reverts commit db79b4fbad0fb7acf435444e0c859a0f028222a4.
2019-08-27 Corrected version of PagingDrHowardEtAl.
2019-08-27 Corrected version of PagingDrHowardEtA.
2019-08-28 PagingDrHowardEtAl, using an UNO R3
2019-08-29 Finalized PagingDrHowardEtAl.ino
2019-09-27 Add Life2.
2019-09-27 Started adding starting patterns.
2019-09-27 Added power distribution board.
2019-09-28 Add Fritzing version of HelloWorld.
2019-09-28 Minor fix (wire rearanging) on HelloWorld's Fritzing breadboard.
2019-09-28 Added fritzing files for WelcomeToGothemCity and PagingDrHowardEtAl.
2019-09-29 Life2 program completed (not tested!).
2019-09-29 Finalize Life2 wiring.
2019-09-29 Finalize Life2 code.
2019-09-29 Finalize OnlyHerHairdresser wiring.
2019-09-30 Add SprocketFactory Fritzing.
2022-07-09 Updates to Only Her Hair Dresser.
2022-07-09 Minor touchups. Small Documentation fixes.
2022-07-09 Remove unused files.
2022-07-09 WhyDidTheChicken => Fritzing.
2022-07-10 Lamp On/Off values and timings move to constants.
2022-07-10 Update BB for WhyDidTheChicken. Create BB Image.
2022-07-10 Add 3D printed parts.
2022-07-11 ComputeFrames -- compute how much frame moulding stock to get.
2022-07-11 Add additional 3D printed parts.
2022-07-11 Add walk legend on walk button.
2022-08-14 Update walk button.
2022-08-18 Start on Teensy 4.0/4.1 + SmartLED Shield for Teensy 4 for Life 2 (128x128 -- 2x 64x128).
2022-08-19 Mostly complete Teensy 4.x Life.
2023-05-31 Add Readme.
2023-05-31 Add Readmes.
